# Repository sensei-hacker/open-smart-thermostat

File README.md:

# Open Smart Thermostat (XIAO RP2040 + M5Stack Dial)

A 24 VAC HVAC thermostat board. A Seeed XIAO RP2040 handles temperature control and switches the HVAC wires through optically isolated triacs. An M5Stack Dial provides the user interface.

KiCad 10 project. All parts are through-hole for hand assembly.

## Hardware
- **Outputs:** 7 channels: G, Y1, Y2, O/B (switched from Rc) and W1, W2, E (switched from Rh).
  - Each channel is a MOC3063 zero-cross optotriac driving a BT138-600E triac with an RC snubber.
  - JP1 links Rh to Rc for single-transformer systems.
- **Power:**
  - Half-wave rectified from Rc/C (1N4007) with a P6KE47CA TVS and an MF-R050 PTC fuse.
  - A TIP122 + 30 V zener pre-clamp (about 29 V max) feeds a Mornsun K7805-500R3 5 V switching module.
  - The Dial is powered from 5 V through J9 and a USB-C pigtail.
- **Sensors:**
  - an on-board DS18B20 (U3)
  - J8 for a remote DS18B20 probe
  - J3 I2C port (GND / 3V3 / SDA / SCL) for a humidity module such as an AHT20 or SHT31

## Files
| Path | What |
|---|---|
| `thermostat.kicad_sch`, `thermostat.kicad_pcb`, `thermostat.kicad_pro`, `thermostat.kicad_dru` | KiCad 10 project |
| `fab/`, `thermostat-fab-*.zip` | Gerbers, Excellon drills and previews (JLCPCB-ready) |
| `BOM-LCSC.csv` | Purchasing BOM with LCSC part numbers, plus "buy elsewhere" items |
| `BOM.csv`, `CPL.csv` | JLCPCB-format BOM and placement files |
| `ASSEMBLY-AND-TEST.md` | Staged build and bench-test procedure, and firmware requirements |
| `DESIGN-REVIEW-*.md`, `STATUS-NEXT-STEPS.md` | Design reviews and change log |
| `sim/` | ngspice models, and a script that builds a SPICE netlist from the schematic's Sim fields (`cd sim && python3 schematic_to_spice.py && python3 plot_schematic_run.py`) |

The M5Stack Dial schematic is available from M5Stack's documentation site.

## Status
- The board is designed and DRC-clean, but **not yet built or tested**.
- Bench-test the MOC3063/triac channels with a real 24 VAC relay or contactor coil before installing (see `ASSEMBLY-AND-TEST.md`).

## Firmware requirement
Set the RP2040 GPIO drive strength to **12 mA** on the seven output pins (GP26, GP27, GP28, GP29, GP4, GP3, GP2), or the MOC3063 LEDs may not trigger reliably.

## Safety
- This connects to HVAC equipment.
- Turn off power at the furnace or air handler before wiring.
- Use at your own risk.

## License
MIT. See `LICENSE`.

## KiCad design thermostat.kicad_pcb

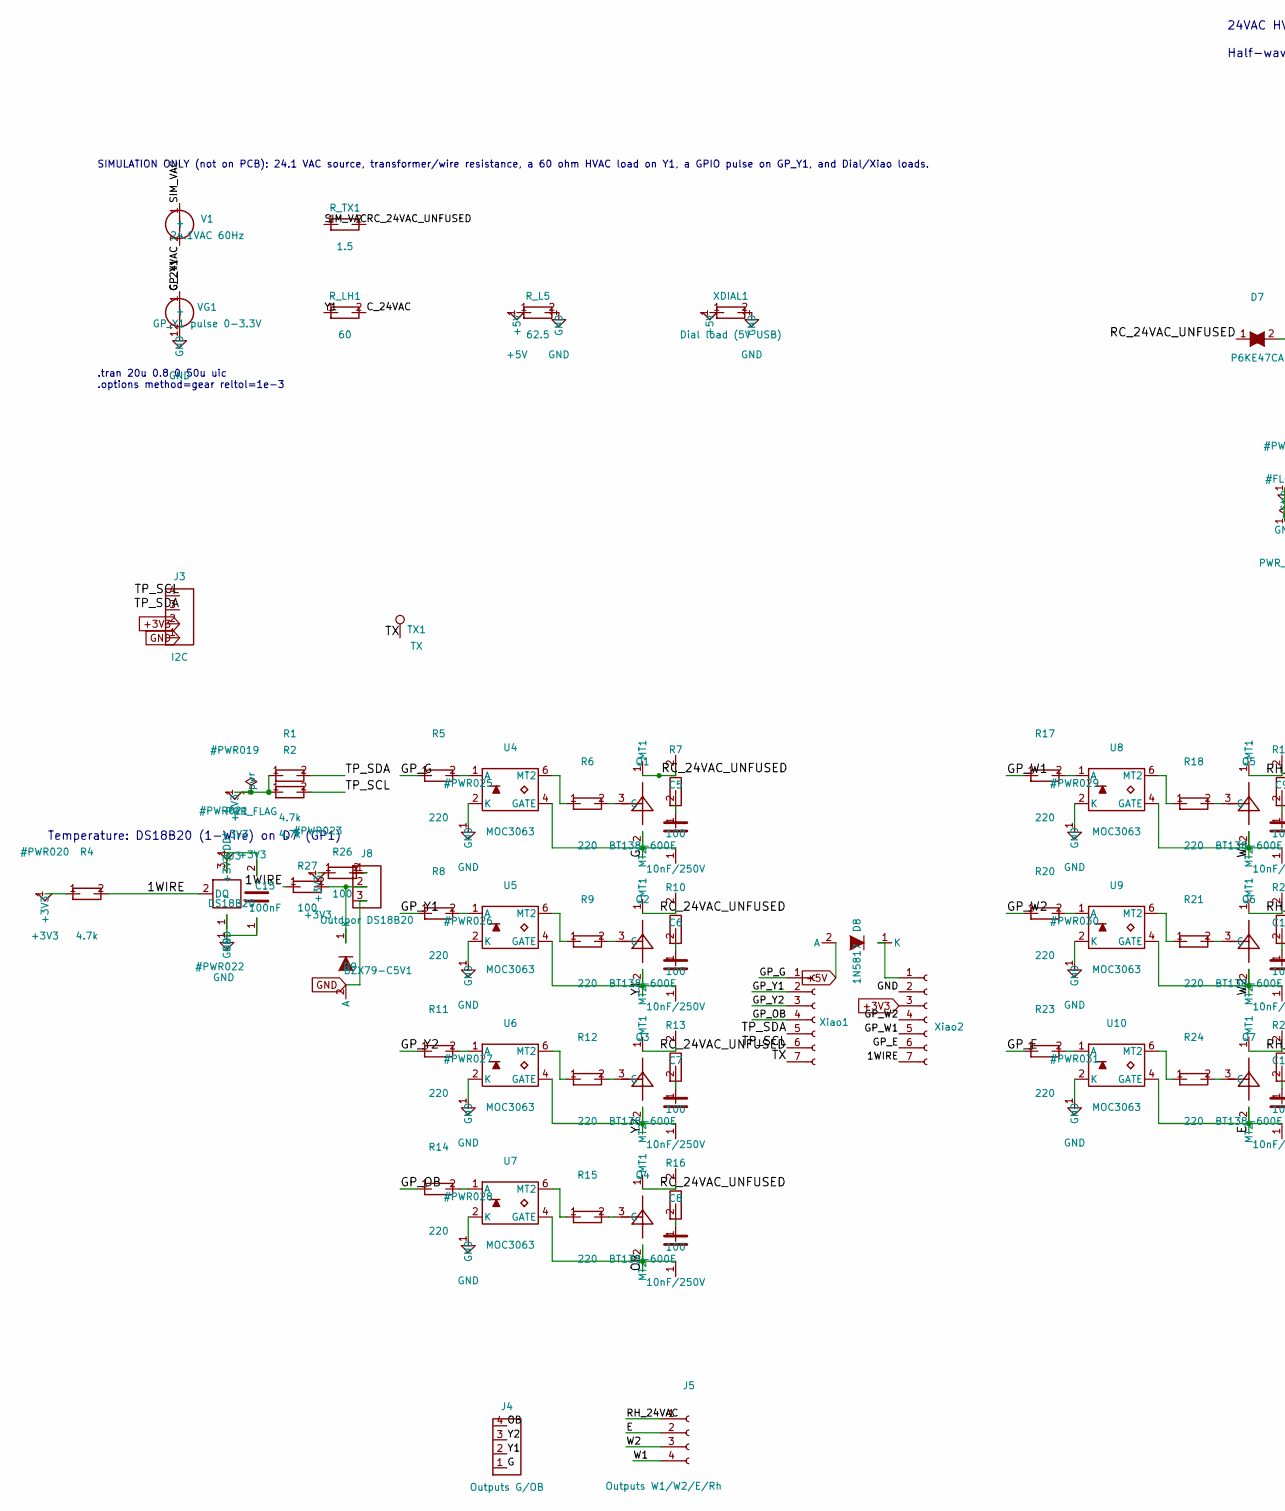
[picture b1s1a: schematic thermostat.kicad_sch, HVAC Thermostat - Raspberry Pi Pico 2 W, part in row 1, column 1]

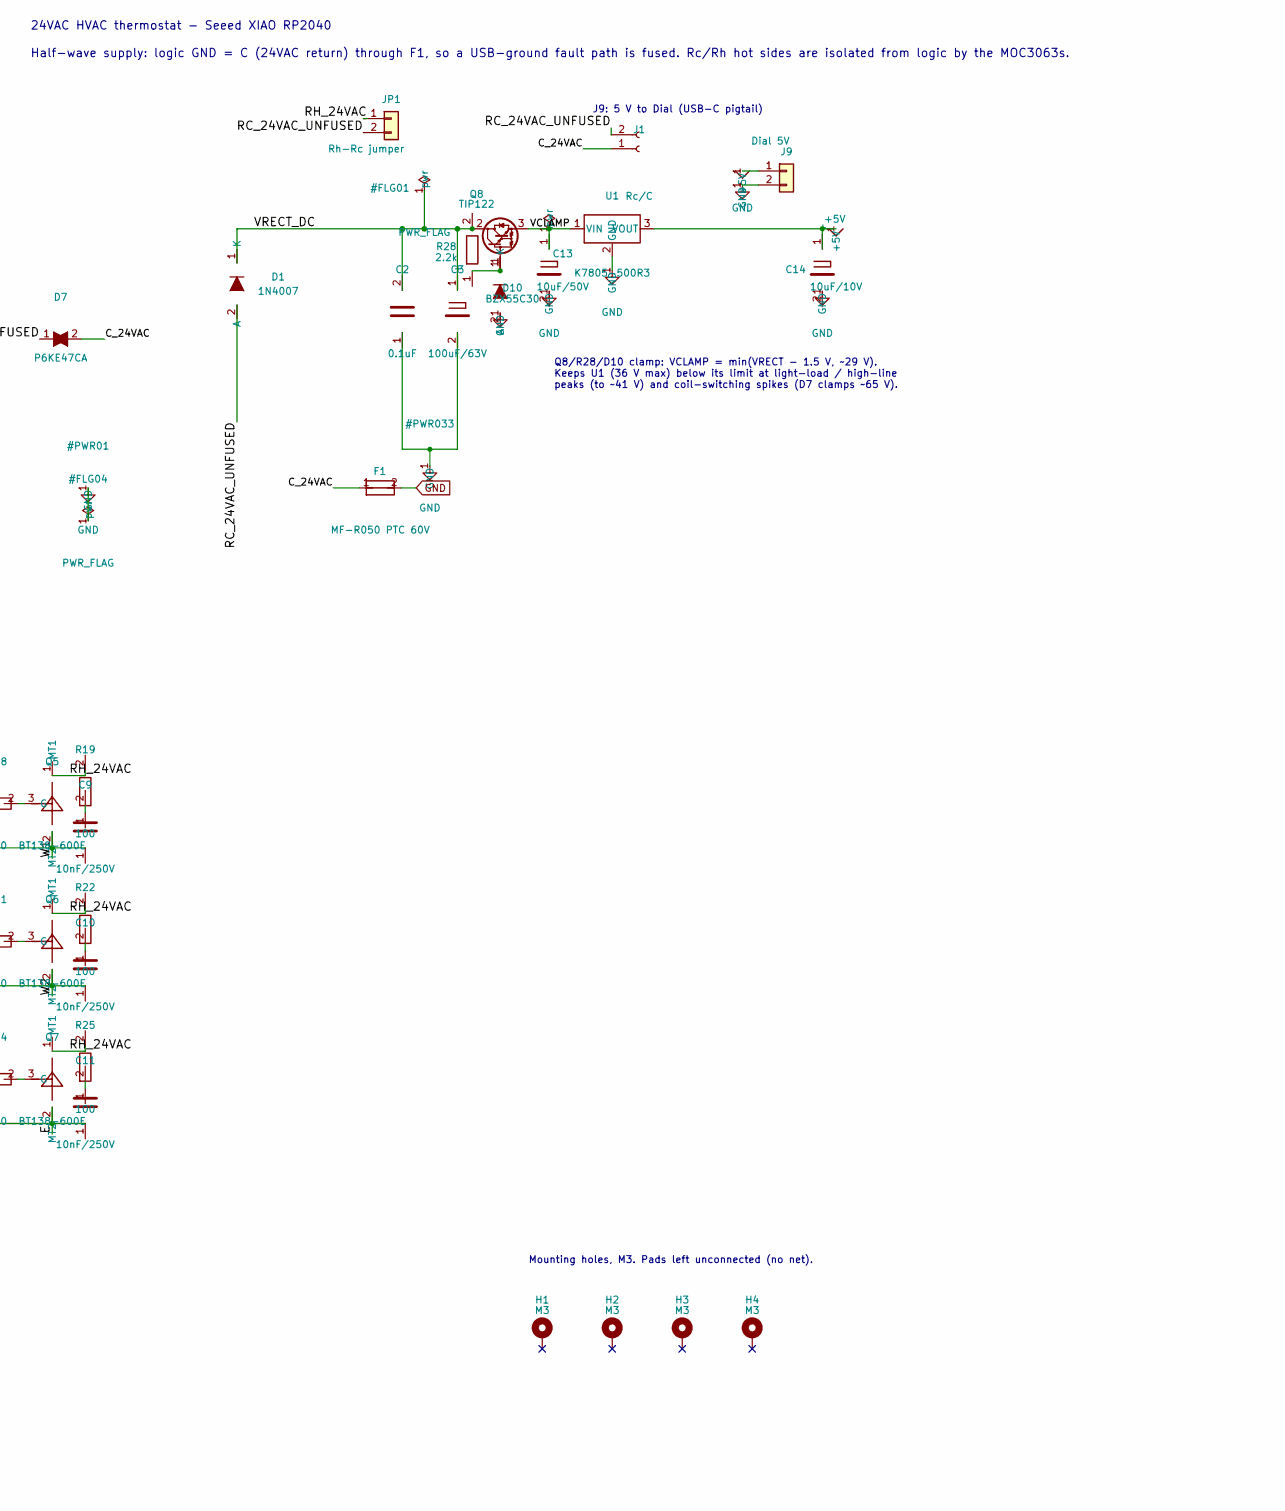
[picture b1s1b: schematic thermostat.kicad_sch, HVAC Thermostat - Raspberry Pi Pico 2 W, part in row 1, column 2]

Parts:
C2: 0.1uF; C_Disc_D5.0mm_W2.5mm_P5.00mm
C3: 100uF/63V; CP_Radial_D8.0mm_P3.50mm
C5, C6, C7, C8, C9, C10, C11: 10nF/250V; C_Rect_L10.3mm_W4.5mm_P7.50mm_MKS4
C13: 10uF/50V; CP_Radial_D5.0mm_P2.00mm
C14: 10uF/10V; CP_Radial_D5.0mm_P2.00mm
C15: 100nF; C_Disc_D3.0mm_W1.6mm_P2.50mm
D1: 1N4007; D_DO-41_SOD81_P10.16mm_Horizontal
D7: P6KE47CA; D_DO-15_P12.70mm_Horizontal
D8: 1N5817; D_DO-41_SOD81_P7.62mm_Horizontal
D9: BZX79-C5V1; D_DO-35_SOD27_P7.62mm_Horizontal
D10: BZX55C30; D_DO-35_SOD27_P7.62mm_Horizontal
F1: MF-R050 PTC 60V; Fuse_Bourns_MF-RHT050
H1, H2, H3, H4: M3; MountingHole_3.2mm_M3_DIN965_Pad
J1: Rc/C; TerminalBlock_Xinya_XY308-2.54-2P_1x02_P2.54mm_Horizontal
J3: I2C; PinHeader_1x04_P2.54mm_Vertical
J4: Outputs G/OB; TerminalBlock_Xinya_XY308-2.54-4P_1x04_P2.54mm_Horizontal
J5: Outputs W1/W2/E/Rh; TerminalBlock_Xinya_XY308-2.54-4P_1x04_P2.54mm_Horizontal
J6: Xiao1; PinHeader_1x07_P2.54mm_Vertical
J7: Xiao2; PinHeader_1x07_P2.54mm_Vertical
J8: Outdoor DS18B20; TerminalBlock_Xinya_XY308-2.54-3P_1x03_P2.54mm_Horizontal
J9: Dial 5V; PinHeader_1x02_P2.54mm_Vertical
JP1: Rh-Rc jumper; PinHeader_1x02_P2.54mm_Vertical
Q1, Q2, Q3, Q4, Q5, Q6, Q7: BT138-600E; TO-220-3_Vertical
Q8: TIP122; TO-220-3_Vertical
R1, R2, R4: 4.7k; R_Axial_DIN0207_L6.3mm_D2.5mm_P5.08mm_Vertical
R5, R6, R8, R9, R11, R12, R14, R15, R17, R18, R20, R21, R23, R24: 220; R_Axial_DIN0207_L6.3mm_D2.5mm_P5.08mm_Vertical
R7, R10, R13, R16, R19, R22, R25, R26, R27: 100; R_Axial_DIN0207_L6.3mm_D2.5mm_P5.08mm_Vertical
R28: 2.2k; R_Axial_DIN0207_L6.3mm_D2.5mm_P5.08mm_Vertical
R_L5: 62.5
R_LH1: 60
R_TX1: 1.5
TX1: TX; TestPoint_THTPad_D2.0mm_Drill1.0mm
U1: K7805-500R3; Converter_DCDC_RECOM_R-78HB-0.5_THT
U3: DS18B20; TO-92_Inline
U4, U5, U6, U7, U8, U9, U10: MOC3063; DIP-6_W7.62mm_Socket
V1: 24.1VAC 60Hz
VG1: GP_Y1 pulse 0-3.3V
XDIAL1: Dial load (5V USB)

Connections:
+3V3: C15.2, J3.2, J7.3, R1.1, R2.1, R4.1, R26.1, U3.3 (VDD)
+5V: C14.1 (+_1), D8.2 (A), J9.1, R_L5.1, U1.3 (VOUT), XDIAL1.1
/1WIRE: J7.7, R4.2, R27.1, U3.2 (DQ)
/C_24VAC: D7.2, F1.1, J1.1, R_LH1.2, V1.2 (-)
/E: C11.1, J5.2, Q7.2 (MT2), U10.4 (GATE)
/G: C5.1, J4.1, Q1.2 (MT2), U4.4 (GATE)
/GP_E: J7.6, R23.1
/GP_G: J6.1, R5.1
/GP_OB: J6.4, R14.1
/GP_W1: J7.5, R17.1
/GP_W2: J7.4, R20.1
/GP_Y1: J6.2, R8.1, VG1.1 (+)
/GP_Y2: J6.3, R11.1
/OB: C8.1, J4.4, Q4.2 (MT2), U7.4 (GATE)
/RC_24VAC_UNFUSED: D1.2 (A), D7.1, J1.2, JP1.2, Q1.1 (MT1), Q2.1 (MT1), Q3.1 (MT1), Q4.1 (MT1), R7.2, R10.2, R13.2, R16.2, R_TX1.2
/RH_24VAC: J5.1, JP1.1, Q5.1 (MT1), Q6.1 (MT1), Q7.1 (MT1), R19.2, R22.2, R25.2
/TP_SCL: J3.4, J6.6, R2.2
/TP_SDA: J3.3, J6.5, R1.2
/TX: J6.7, TX1.1 (1_1)
/VCLAMP: C13.1 (+_1), Q8.3 (E), U1.1 (VIN)
/VRECT_DC: C2.2, C3.1 (+_1), D1.1 (K), Q8.2 (C), R28.2
/W1: C9.1, J5.4, Q5.2 (MT2), U8.4 (GATE)
/W2: C10.1, J5.3, Q6.2 (MT2), U9.4 (GATE)
/Y1: C6.1, J4.2, Q2.2 (MT2), R_LH1.1, U5.4 (GATE)
/Y2: C7.1, J4.3, Q3.2 (MT2), U6.4 (GATE)
GND: C2.1, C3.2, C13.2, C14.2, C15.1, D9.2 (A), D10.2 (A), F1.2, J3.1, J7.2, J8.3, J9.2, R_L5.2, U1.2 (GND), U3.1 (GND), U4.2 (K), U5.2 (K), U6.2 (K), U7.2 (K), U8.2 (K), U9.2 (K), U10.2 (K), VG1.2 (-), XDIAL1.2
unnamed: C5.2, R7.1
unnamed: C6.2, R10.1
unnamed: C7.2, R13.1
unnamed: C8.2, R16.1
unnamed: C9.2, R19.1
unnamed: C10.2, R22.1
unnamed: C11.2, R25.1
unnamed: D8.1 (K), J7.1
unnamed: D9.1 (K), J8.2, R27.2
unnamed: D10.1 (K), Q8.1 (B), R28.1
unnamed: J8.1, R26.2
unnamed: Q1.3 (G), R6.2
unnamed: Q2.3 (G), R9.2
unnamed: Q3.3 (G), R12.2
unnamed: Q4.3 (G), R15.2
unnamed: Q5.3 (G), R18.2
unnamed: Q6.3 (G), R21.2
unnamed: Q7.3 (G), R24.2
unnamed: R_TX1.1, V1.1 (+)
unnamed: R5.2, U4.1 (A)
unnamed: R6.1, U4.6 (MT2)
unnamed: R8.2, U5.1 (A)
unnamed: R9.1, U5.6 (MT2)
unnamed: R11.2, U6.1 (A)
unnamed: R12.1, U6.6 (MT2)
unnamed: R14.2, U7.1 (A)
unnamed: R15.1, U7.6 (MT2)
unnamed: R17.2, U8.1 (A)
unnamed: R18.1, U8.6 (MT2)
unnamed: R20.2, U9.1 (A)
unnamed: R21.1, U9.6 (MT2)
unnamed: R23.2, U10.1 (A)
unnamed: R24.1, U10.6 (MT2)

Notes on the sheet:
SIMULATION ONLY (not on PCB): 24.1 VAC source, transformer/wire resistance, a 60 ohm HVAC load on Y1, a GPIO pulse on GP_Y1, and Dial/Xiao loads.
Half-wave supply: logic GND = C (24VAC return) through F1, so a USB-ground fault path is fused. Rc/Rh hot sides are isolated from logic by the MOC3063s.
Mounting holes, M3. Pads left unconnected (no net).
J9: 5 V to Dial (USB-C pigtail)
Temperature: DS18B20 (1-Wire) on D7 (GP1)
24VAC HVAC thermostat - Seeed XIAO RP2040
.tran 20u 0.8 0 50u uic .options method=gear reltol=1e-3
Q8/R28/D10 clamp: VCLAMP = min(VRECT - 1.5 V, ~29 V). Keeps U1 (36 V max) below its limit at light-load / high-line peaks (to ~41 V) and coil-switching spikes (D7 clamps ~65 V).

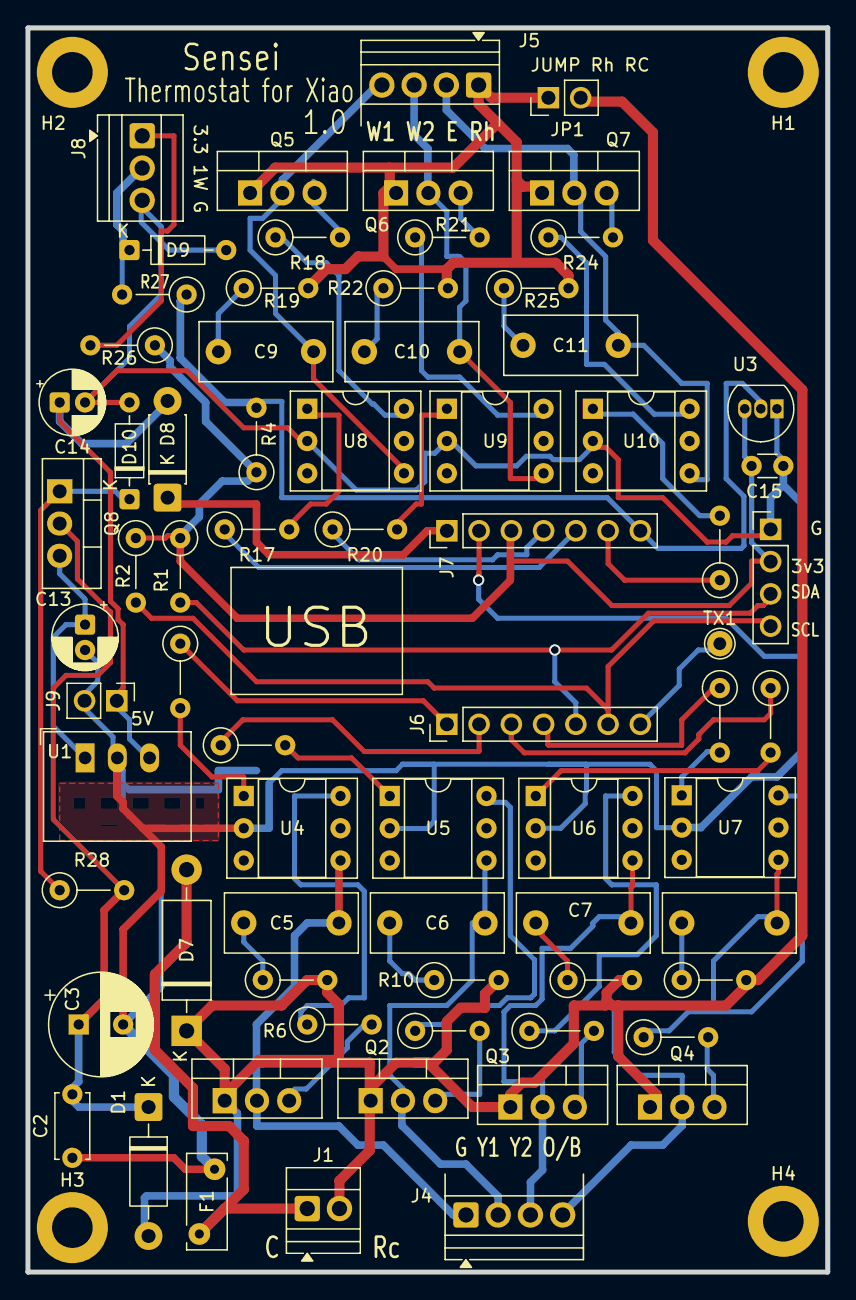
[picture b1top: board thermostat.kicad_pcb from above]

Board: 2 copper layers, 63.0 x 98.0 mm, 76 parts (0 on the bottom side), 58 nets.

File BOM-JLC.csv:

Comment,Designator,Footprint,LCSC Part #
Capacitor 100nF 100V ceramic,C2,CAP-TH_L5.0-W2.5-P5.00,C454377
Capacitor 100nF 50V ceramic,C15,CAP-TH_L3.0-W1.6-P2.50,C168753
Capacitor 100uF 63V electrolytic,C3,CAP-TH_BD8.0-P3.50,C88774
Capacitor 10nF 630V film,"C5,C6,C7,C8,C9,C10,C11",CAP-TH_L10.3-W4.5-P7.50,C2927902
Capacitor 10uF 50V electrolytic,"C13,C14",CAP-TH_BD5.0-P2.00,C88833
Diode 1N4007 rectifier 1A 1000V,D1,DO-41_P10.16-H,C53568
Diode TVS P6KE47CA bidirectional,D7,DO-15_P12.70-H,C8929
Diode 1N5817 Schottky 1A 20V,D8,DO-41_P7.62-H,C698892
Diode zener 5.1V 0.5W,D9,DO-35_P7.62-H,C895329
Diode zener 30V 0.5W,D10,DO-35_P7.62-H,C5190031
Fuse PTC resettable 0.5A 60V,F1,FUSE-TH_P5.10,C208476
Terminal block 2P 2.54mm,J1,CONN-TH_2P-P2.54_XY308,C557685
Terminal block 3P 2.54mm,J8,CONN-TH_3P-P2.54_XY308,C557686
Terminal block 4P 2.54mm,"J4,J5",CONN-TH_4P-P2.54_XY308,C915913
Male header 2P,"J9,JP1",HDR-TH_2P-P2.54-V,C32713268
Male header 4P,J3,HDR-TH_4P-P2.54-V,C32713270
Male header 7P,"J6,J7",HDR-TH_7P-P2.54-V,C32713273
Triac BT138-600E 12A 600V,"Q1,Q2,Q3,Q4,Q5,Q6,Q7",TO-220-3_L10.0-W4.5-P2.54-T,C14796
Transistor TIP122 NPN Darlington,Q8,TO-220-3_L10.0-W4.5-P2.54-T,C16283
Resistor 4.7K,"R1,R2,R4",RES-TH_BD2.5-L6.3-P5.08-V,C57204
Resistor 220R,"R5,R6,R8,R9,R11,R12,R14,R15,R17,R18,R20,R21,R23,R24",RES-TH_BD2.5-L6.3-P5.08-V,C57439
Resistor 100R,"R7,R10,R13,R16,R19,R22,R25,R26,R27",RES-TH_BD2.5-L6.3-P5.08-V,C57438
Resistor 2.2K,R28,RES-TH_BD2.5-L6.3-P5.08-V,C58595
DC-DC module 5V 0.5A,U1,SIP-3_L11.6-W7.5-P2.54,C86735
Temperature sensor DS18B20,U3,TO-92-3_P1.27-INLINE,C9753
Optotriac MOC3063 zero-cross,"U4,U5,U6,U7,U8,U9,U10",DIP-6_L8.9-W6.6-P2.54-LS7.6,C8920

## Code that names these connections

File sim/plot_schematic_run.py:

import numpy as np, matplotlib
matplotlib.use('Agg'); import matplotlib.pyplot as plt
d=np.loadtxt('from_schematic.dat'); t=d[:,0]
names=['RC_24VAC_UNFUSED','C_24VAC','VRECT_DC','VCLAMP','+5V','Y1','GP_Y1']
v=dict(zip(names,d[:,1:9].T))
v['Yload']=v['Y1'];v['AC']=v['RC_24VAC_UNFUSED']
ss=(t>0.1)&(t<0.2)
print('VRECT_DC %.1f..%.1f V  VCLAMP %.1f..%.1f V  +5V %.3f V'%(v['VRECT_DC'][ss].min(),v['VRECT_DC'][ss].max(),v['VCLAMP'][ss].min(),v['VCLAMP'][ss].max(),v['+5V'][ss].mean()))
for a,b,lab in ((0.1,0.19,'GPIO low (before 0.2 s)'),(0.3,0.49,'GPIO high (0.2-0.5 s)'),(0.6,0.79,'GPIO low again')):
    m=(t>a)&(t<b);y=v['Yload'][m]   # Y1 vs gnd node; load returns to C
    print('%-26s load voltage pk %.1f V  rms %.1f V'%(lab,abs(y).max(),np.sqrt((y**2).mean())))
fig,ax=plt.subplots(3,1,figsize=(11,9))
ax[0].plot(t,v['AC'],lw=.5,label='24VAC (Rc to C)');ax[0].plot(t,v['VRECT_DC'],label='VRECT_DC');ax[0].plot(t,v['VCLAMP'],label='VCLAMP');ax[0].plot(t,v['+5V'],label='+5V');ax[0].legend(loc='right');ax[0].grid(1);ax[0].set_title('Power chain')
ax[1].plot(t,v['GP_Y1'],label='GP_Y1 (GPIO)');ax[1].plot(t,v['Yload'],lw=.6,label='load voltage (Y1 to C)');ax[1].legend();ax[1].grid(1);ax[1].set_title('Relay channel Y1')
m=(t>0.18)&(t<0.28);ax[2].plot(t[m],v['Yload'][m],label='load voltage');ax[2].plot(t[m],v['AC'][m],alpha=.4,label='24VAC at terminals');ax[2].legend();ax[2].grid(1);ax[2].set_title('Zoom: turn-on at zero crossing');ax[2].set_xlabel('s')
plt.tight_layout();plt.savefig('from_schematic.png',dpi=80)
